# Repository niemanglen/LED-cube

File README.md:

# LED-cube

The LED-cube is a cube formed from printed circuit boards whose faces are covered in WS2812B leds. This project contains the hardware and software used.

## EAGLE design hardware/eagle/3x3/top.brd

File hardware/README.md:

Shipping will add up very quickly. The lead time on the ATMEGA's from newark can be a bit unpredictable. I recommend buying extra supplies in case some get messed up. Getting more of the pcb's does not greatly increase their price. Consider getting multiple pcb's and building more than one cube. The Memory IC is also optional and not currently used in the code.

# Parts vendors:

Tayda electronics (taydaelectronics.com)

| Part | Part Number | Quantity | Price ea | Price |
| :---: | :---: | :---: | :---: | :---: |
| Right Angle Female | A-1667 | 7 | 0.15 | 1.05 |
| 40 pin Male | A-197 | 2 | 0.15 | 0.30 |
| 40 pin Right Angle | A-199 | 1 | 0.17 | 0.17 |
| Tact Switch | A-5127 | 4 | 0.04 | 0.16 |
| Slide Switch | A-5104 | 1 | 0.22 | 0.22 |
| 10K pullup | A-3089 | 50 | 0.01 | 0.50 |
| Memory IC | A-4643 | 1 | 0.89 | 0.89 |
| Battery Holder | A-3340 | 1 | 0.27 | 0.27 |
| Battery Conn. Female | A-826 | 1 | 0.02 | 0.02 |
| Battery Conn. Male | A-804 | 1 | 0.02 | 0.02 |
| Crimp | A-837 | 2 | 0.03 | 0.06 |

Newark (newark.com)

| Part | Part Number | Quantity | Price ea | Price |
| :---: | :---: | :---: | :---: | :---: |
| ATMEGA328PB-AU | 58Y6083 | 1 | 1.61 | 1.61 |

Amazon (amazon.com)

| Part | Part Number | Quantity | Price ea | Price |
| :---: | :---: | :---: | :---: | :---: |
| WS2812B | --- | 100 | ~0.10 | ~10.00 |

JLC PCB (jlcpcb.com)

| Part | Part Number | Quantity | Price ea | Price |
| :---: | :---: | :---: | :---: | :---: |
| Side PCB | --- | 4 | --- | 2.00 |
| Top PCB | --- | 1 | --- | 4.00 |
| Bottom PCB | --- | 1 | --- | 4.00 |

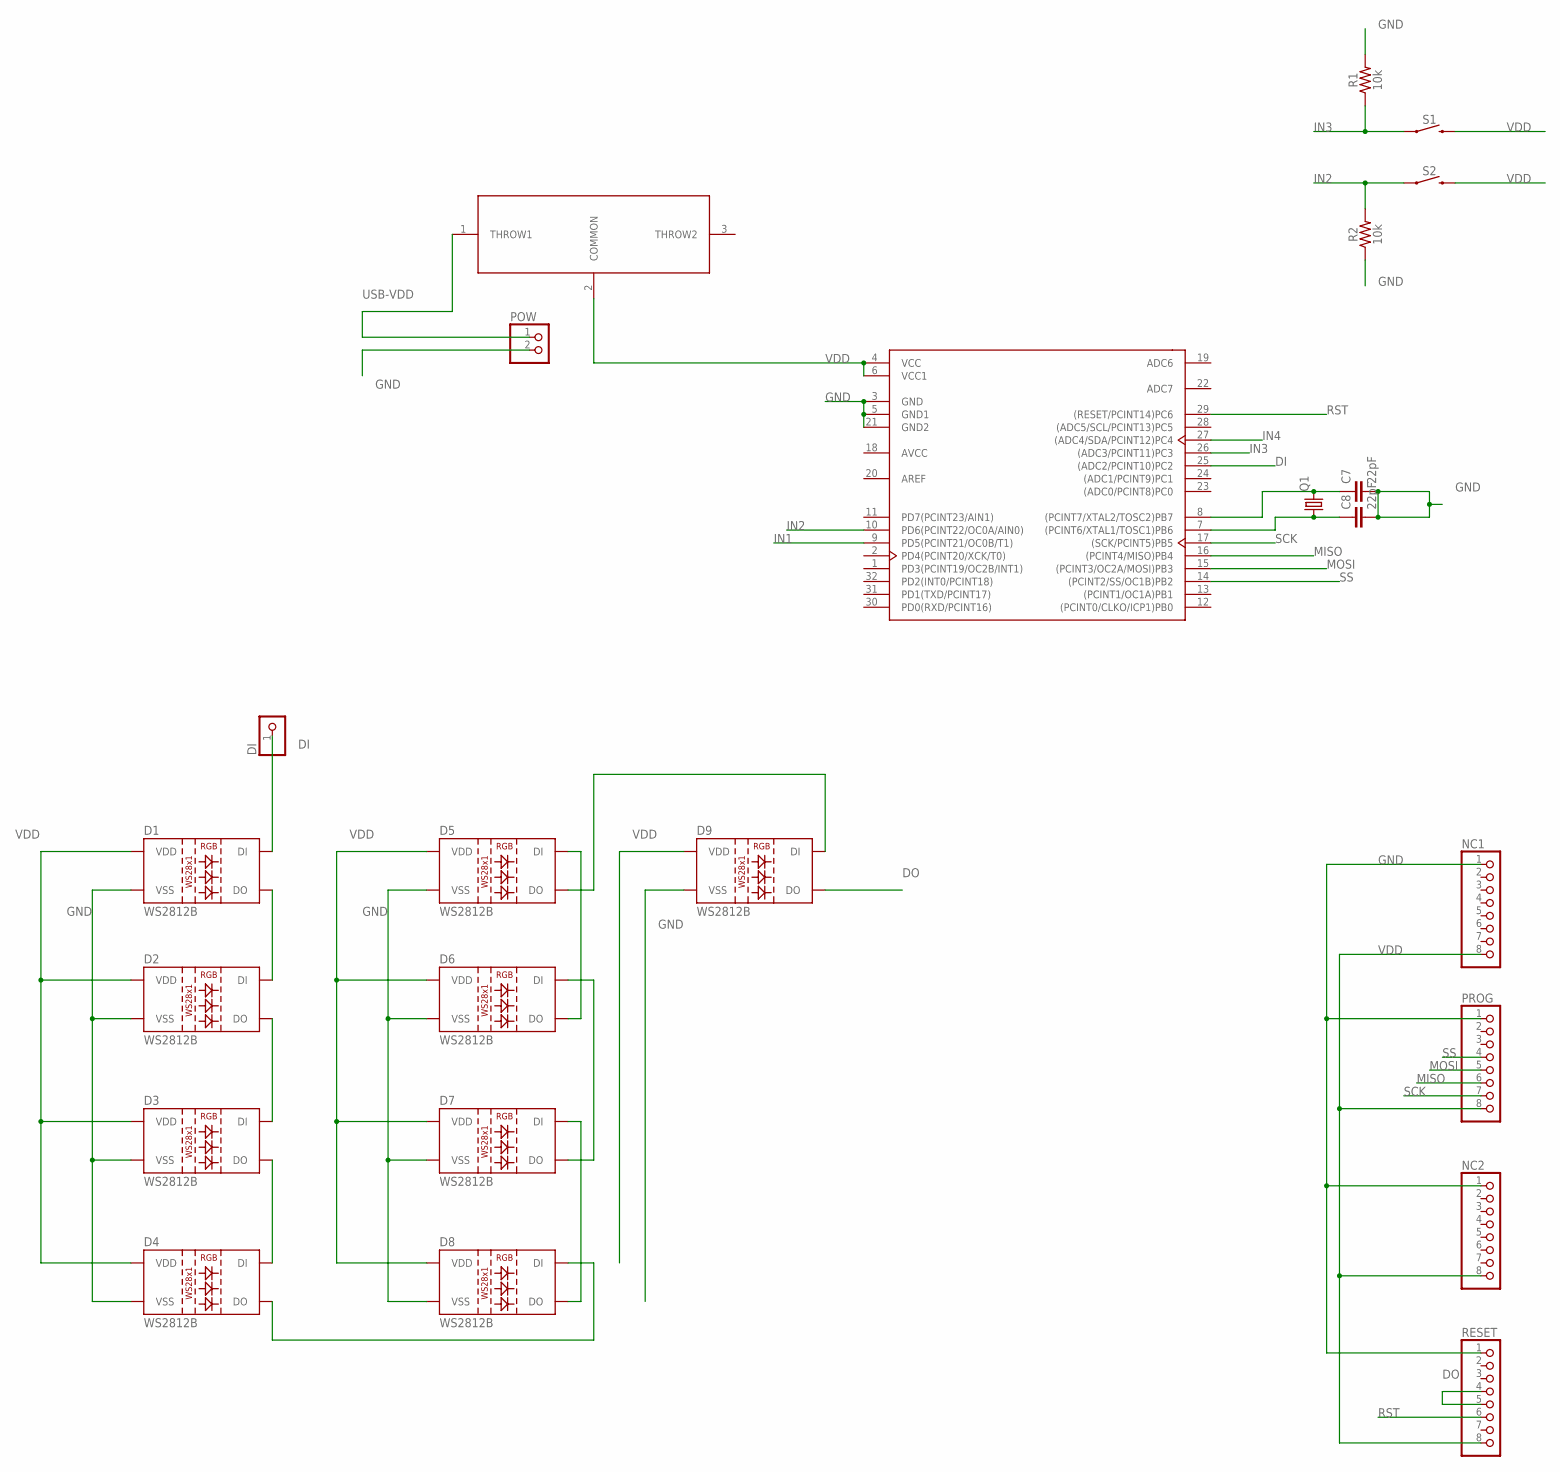
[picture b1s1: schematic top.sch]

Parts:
C7, C8: 22pF; 0805
D1, D2, D3, D4, D5, D6, D7, D8, D9: WS2812B
DI: PINHD-1X1; 1X01
IC1: ATMEGA328P-AU; TQFP-32
NC1, NC2: PINHD-1X8; 1X08
POW: PINHD-1X2; 1X02
PROG: PINHD-1X8; 1X08
Q1: CRYSTALHC49S; HC49/S
R1, R2: 10k; 0805
RESET: PINHD-1X8; 1X08
S1, S2: MOMENTARY-SWITCH-SPST-PTH-6.0MM; TACTILE_SWITCH_PTH_6.0MM
U$2: SLIDE_SWITCH_1P2T

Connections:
AREF: IC1.20 (AREF)
AVCC: IC1.18 (AVCC)
DI: D1.4 (DI), DI.1, IC1.25 ((ADC2/PCINT10)PC2)
DO: D9.2 (DO), RESET.4, RESET.5
GND: C7.2, C8.2, D1.3 (VSS), D2.3 (VSS), D3.3 (VSS), D4.3 (VSS), D5.3 (VSS), D6.3 (VSS), D7.3 (VSS), D8.3 (VSS), D9.3 (VSS), IC1.3 (GND), IC1.5 (GND1), IC1.21 (GND2), NC1.1, NC2.1, POW.2, PROG.1, R1.2, R2.1, RESET.1
IN1: IC1.9 (PD5(PCINT21/OC0B/T1))
IN2: IC1.10 (PD6(PCINT22/OC0A/AIN0)), R2.2, S2.1
IN3: IC1.26 ((ADC3/PCINT11)PC3), R1.1, S1.1
IN4: IC1.27 ((ADC4/SDA/PCINT12)PC4)
MISO: IC1.16 ((PCINT4/MISO)PB4), PROG.6
MOSI: IC1.15 ((PCINT3/OC2A/MOSI)PB3), PROG.5
unnamed: D4.2 (DO), D8.4 (DI)
unnamed: D7.4 (DI), D8.2 (DO)
unnamed: D1.2 (DO), D2.4 (DI)
unnamed: D2.2 (DO), D3.4 (DI)
unnamed: D3.2 (DO), D4.4 (DI)
unnamed: D6.4 (DI), D7.2 (DO)
unnamed: D5.2 (DO), D9.4 (DI)
unnamed: C7.1, IC1.8 ((PCINT7/XTAL2/TOSC2)PB7), Q1.2
unnamed: D5.4 (DI), D6.2 (DO)
unnamed: C8.1, IC1.7 ((PCINT6/XTAL1/TOSC1)PB6), Q1.1
RST: IC1.29 ((RESET/PCINT14)PC6), RESET.6
SCK: IC1.17 ((SCK/PCINT5)PB5), PROG.7
SS: IC1.14 ((PCINT2/SS/OC1B)PB2), PROG.4
USB-VDD: POW.1, U$2.1 (THROW1)
VDD: D1.1 (VDD), D2.1 (VDD), D3.1 (VDD), D4.1 (VDD), D5.1 (VDD), D6.1 (VDD), D7.1 (VDD), D8.1 (VDD), D9.1 (VDD), IC1.4 (VCC), IC1.6 (VCC1), NC1.8, NC2.8, PROG.8, RESET.8, S1.3 (2), S2.3 (2), U$2.2 (COMMON)

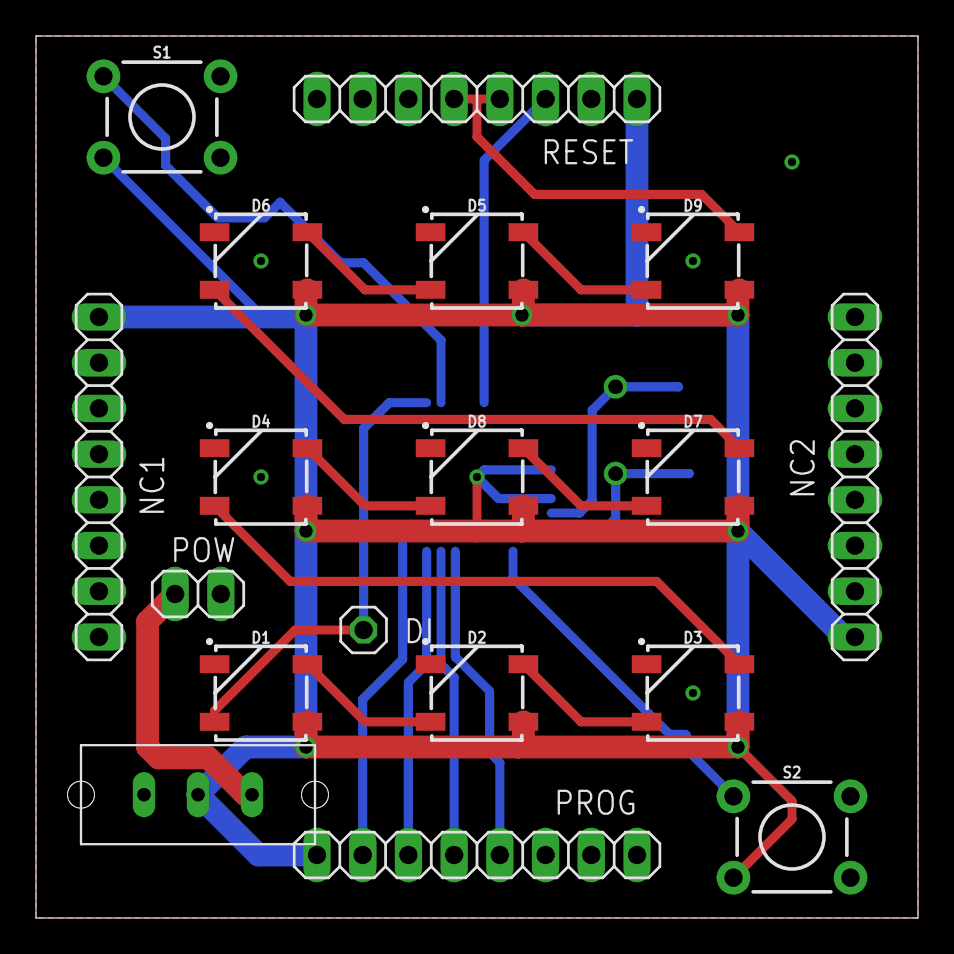
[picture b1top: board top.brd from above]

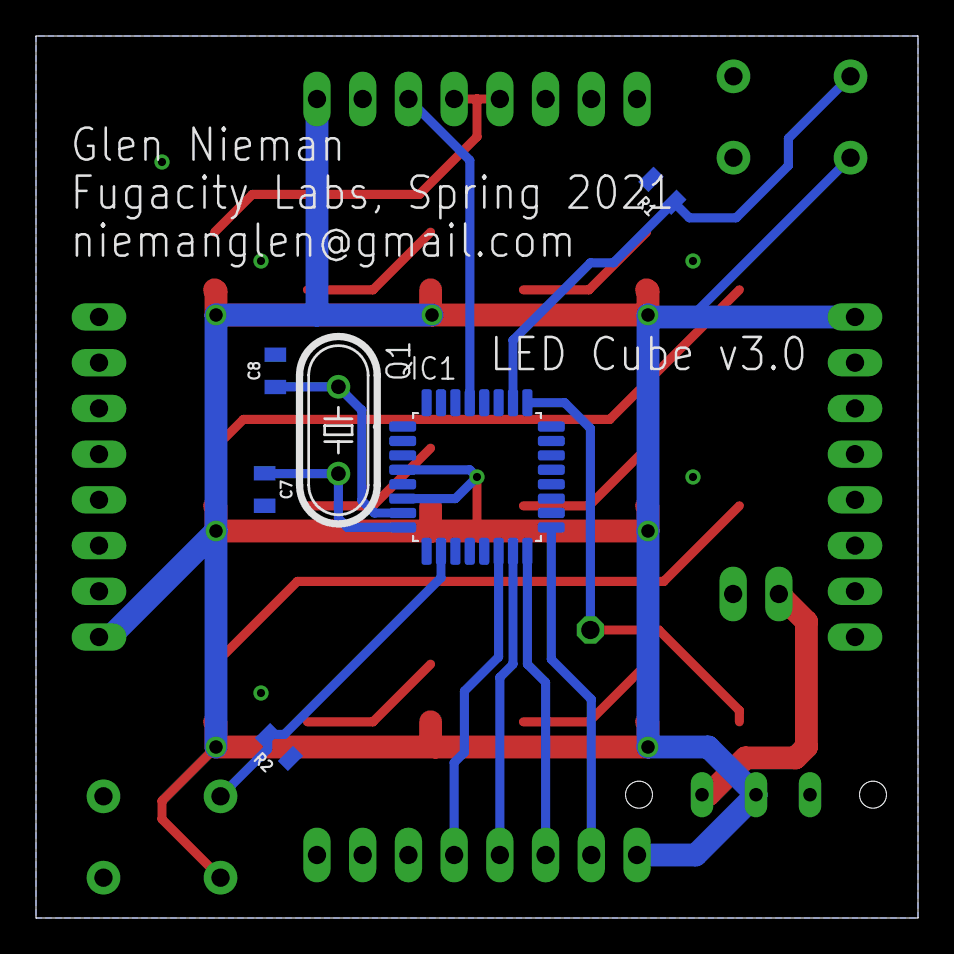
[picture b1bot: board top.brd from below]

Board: 2 copper layers, 49.0 x 49.0 mm, 24 parts (6 on the bottom side), 22 nets.

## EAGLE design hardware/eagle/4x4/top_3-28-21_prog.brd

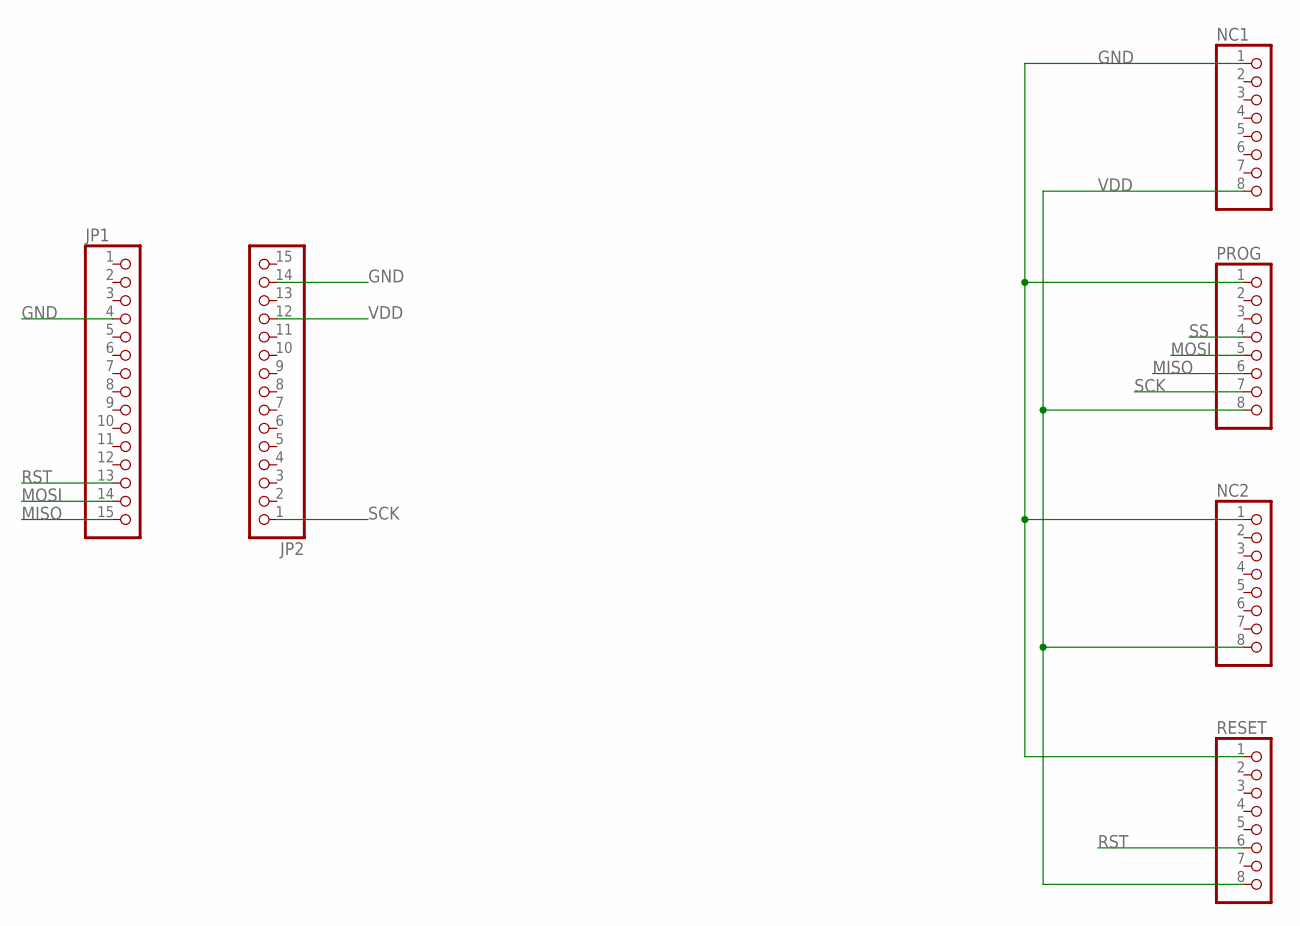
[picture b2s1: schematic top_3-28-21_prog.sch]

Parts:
JP1, JP2: PINHD-1X15; 1X15
NC1, NC2: PINHD-1X8; 1X08
PROG: PINHD-1X8; 1X08
RESET: PINHD-1X8; 1X08

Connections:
GND: JP1.4, JP2.14, NC1.1, NC2.1, PROG.1, RESET.1
MISO: JP1.15, PROG.6
MOSI: JP1.14, PROG.5
RST: JP1.13, RESET.6
SCK: JP2.1, PROG.7
SS: PROG.4
VDD: JP2.12, NC1.8, NC2.8, PROG.8, RESET.8

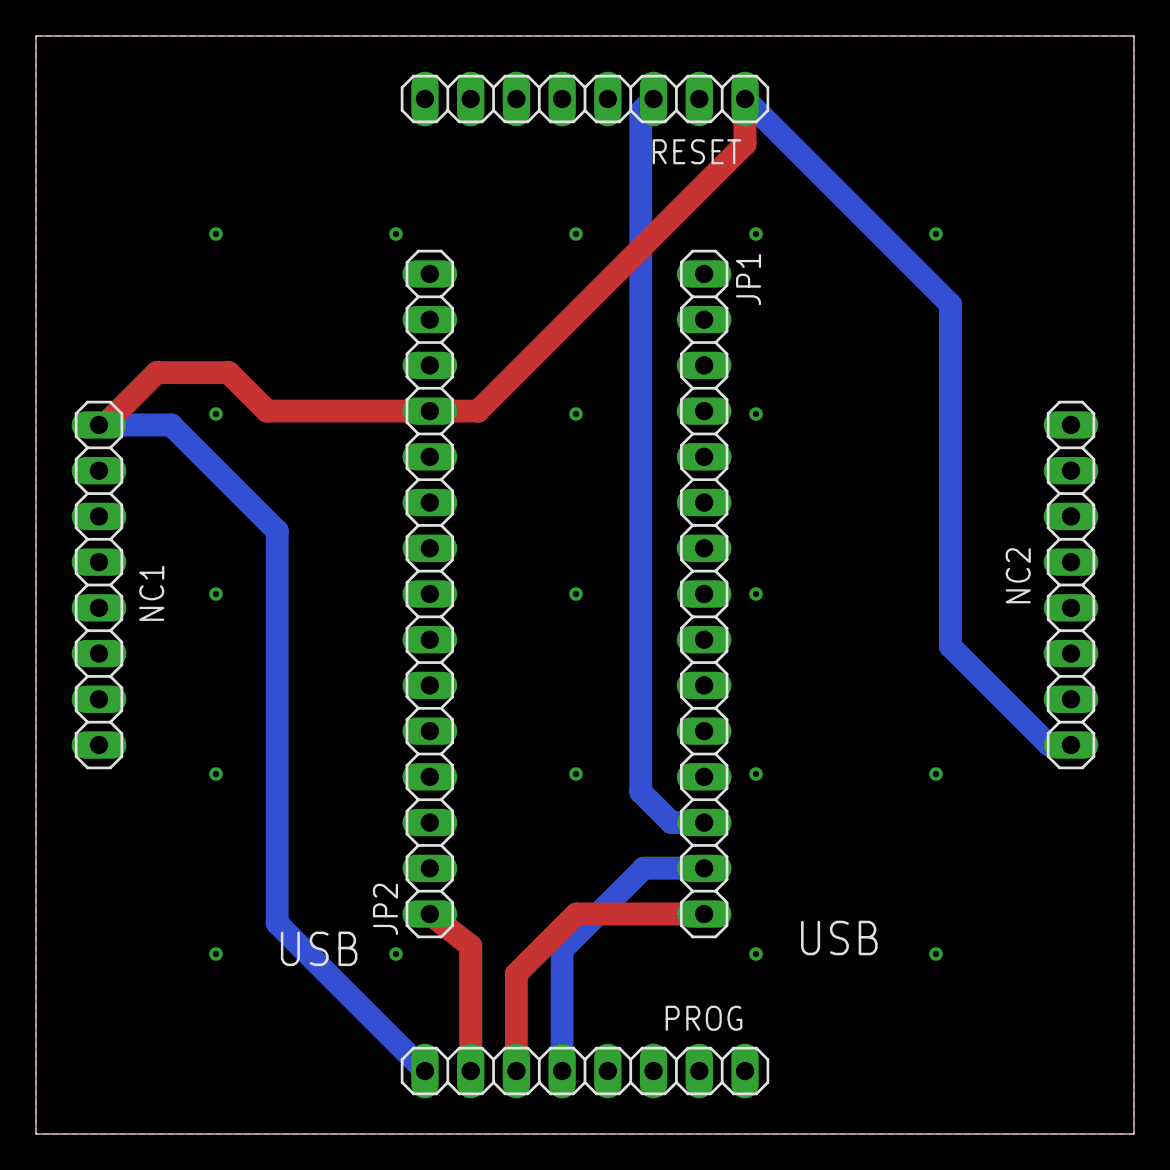
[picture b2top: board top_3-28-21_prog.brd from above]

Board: 2 copper layers, 61.0 x 61.0 mm, 6 parts (0 on the bottom side), 6 nets.

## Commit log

2021-07-18 Create a
2021-07-18 Create eagle
2021-07-18 Create m
2021-07-18 Create 3x3
2021-07-18 Rename bottom_3-28-21.brd to bottom.brd
2021-07-18 Rename bottom_3-28-21.sch to bottom.sch
2021-07-18 Rename top_3-28-21.brd to top.brd
2021-07-18 Rename top_3-28-21.sch to top.sch
2021-07-18 Rename top_3-28-21_prog.brd to top_prog.brd
2021-07-18 Rename top_3-28-21_prog.sch to top_prog.sch
2021-07-18 Rename top_3-28-21m.brd to top_m.brd
2021-07-18 Rename top_3-28-21m.sch to top_m.sch
2021-08-21 Rename software/FIRE.ino to software/v2.0/FIRE.ino
2021-08-21 Rename software/RGB_master_2.0.ino to software/v2.0/RGB_master_2.0.ino
2021-08-21 Rename software/black.ino to software/v2.0/black.ino
2021-08-21 Rename software/color_funcs.ino to software/v2.0/color_funcs.ino
2021-08-21 Rename software/dots_glen.ino to software/v2.0/dots_glen.ino
2021-08-21 Rename software/drops_glen.ino to software/v2.0/drops_glen.ino
2021-08-21 Rename software/mat2arr.ino to software/v2.0/mat2arr.ino
2021-08-21 Rename software/rainbow.ino to software/v2.0/rainbow.ino
2021-08-21 Rename software/rainbow_c.ino to software/v2.0/rainbow_c.ino
2021-08-21 Rename software/rainbow_check.ino to software/v2.0/rainbow_check.ino
2021-08-21 Rename software/rainbow_h.ino to software/v2.0/rainbow_h.ino
2021-08-21 Rename software/user_settings.ino to software/v2.0/user_settings.ino

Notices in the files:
parts and their libraries:
SparkFun-Capacitors: Licensing: Creative Commons ShareAlike 4.0 International - https://creativecommons.org/licenses/by-sa/4.0
